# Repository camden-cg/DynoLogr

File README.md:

# DynoLogr

DynoLogr is an ESP32-based vehicle telemetry project with an OLED interface and
a browser dashboard.

## Repository layout

- `firmware/DynoLogr/` contains the Arduino sketch. `DynoLogr.ino` holds shared
  configuration and state; the other `.ino` tabs group control, IMU, display,
  web API, and application code.
- `firmware/prototypes/` contains the standalone OLED/MPU prototype sketch.
- `software/` contains the browser dashboard and its CSS and JavaScript.
- `electronics/` contains the KiCad board file.
- `docs/images/` contains project images.

## Firmware

Open `firmware/DynoLogr/DynoLogr.ino` in Arduino IDE. This sketch uses
Bluepad32, which requires its ESP32 board package; installing a `Bluepad32`
library in the sketchbook `libraries` folder is not sufficient.

In Arduino IDE settings, add both board package URLs:

- `https://raw.githubusercontent.com/espressif/arduino-esp32/gh-pages/package_esp32_index.json`
- `https://raw.githubusercontent.com/ricardoquesada/esp32-arduino-lib-builder/master/bluepad32_files/package_esp32_bluepad32_index.json`

In Boards Manager, install `esp32` and `esp32_bluepad32`. Then select **DOIT
ESP32 DEVKIT V1** from the **ESP32 + Bluepad32 Arduino** board menu, rather
than selecting the same board from the regular Espressif board menu. See the
[Bluepad32 Arduino setup guide](https://bluepad32.readthedocs.io/en/latest/plat_arduino/).

Install the remaining libraries included by the sketch: Adafruit GFX,
Adafruit SSD1306, Adafruit MPU6050, Adafruit Unified Sensor, ESP32Servo, and
ArduinoJson. The ESP32 Arduino core provides Wire, WiFi, and WebServer.

Copy `firmware/DynoLogr/Credentials.example.h` to
`firmware/DynoLogr/Credentials.h` and set `WIFI_SSID` and `WIFI_PASS` there.
`Credentials.h` is ignored by Git and should remain local. The firmware continues
to run without Wi-Fi.

## Dashboard

Open `software/index.html` in a browser. Connect to the ESP32's network address
using the dashboard connection controls.

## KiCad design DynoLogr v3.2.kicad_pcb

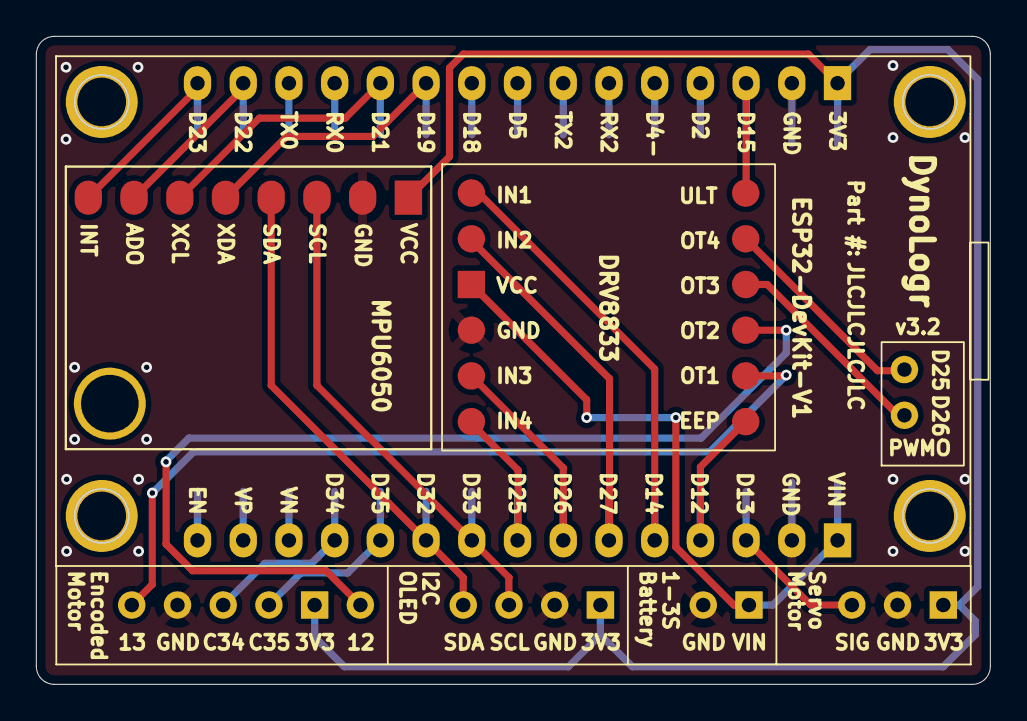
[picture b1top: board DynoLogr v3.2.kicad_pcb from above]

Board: 2 copper layers, 53.0 x 36.0 mm, 4 parts (0 on the bottom side), 25 nets.

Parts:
DRV8833: DRV8833
ESP32, ESP32-DevKit-V1: ESP32 30; ESP32_30pin
MPU6050: MPU6050

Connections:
2: ESP32.2 (D2), ESP32-DevKit-V1.2 (D2)
4: ESP32.4 (D4-), ESP32-DevKit-V1.4 (D4-)
/3V3: ESP32.3V3, ESP32-DevKit-V1.3V3, MPU6050.+ (VCC)
/BO: DRV8833.VCC, ESP32.VIN, ESP32-DevKit-V1.VIN
/EC1: ESP32.34 (D34), ESP32-DevKit-V1.34 (D34)
/EC2: ESP32.35 (D35), ESP32-DevKit-V1.35 (D35)
/EEP: DRV8833.EEP, ESP32.12 (D12), ESP32-DevKit-V1.12 (D12)
/GND: DRV8833.GND, ESP32.GND, ESP32.GND2 (GND), ESP32-DevKit-V1.GND, ESP32-DevKit-V1.GND2 (GND), MPU6050.- (GND)
/IN1: DRV8833.IN1, ESP32.14 (D14), ESP32-DevKit-V1.14 (D14)
/IN2: DRV8833.IN2, ESP32.27 (D27), ESP32-DevKit-V1.27 (D27)
/IN3: DRV8833.IN3, ESP32.26 (D26), ESP32-DevKit-V1.26 (D26)
/IN4: DRV8833.IN4, ESP32.25 (D25), ESP32-DevKit-V1.25 (D25)
/INT: ESP32.23 (D23), ESP32-DevKit-V1.23 (D23), MPU6050.23 (INT)
/SCL: ESP32.33 (D33), ESP32-DevKit-V1.33 (D33), MPU6050.22 (SCL)
/SDA: ESP32.32 (D32), ESP32-DevKit-V1.32 (D32), MPU6050.21 (SDA)
/SPWM: ESP32.13 (D13), ESP32-DevKit-V1.13 (D13)
AD0: ESP32.22 (D22), ESP32-DevKit-V1.22 (D22), MPU6050.3 (ADO)
EN: ESP32.EN, ESP32-DevKit-V1.EN
unnamed: ESP32.5 (D5), ESP32-DevKit-V1.5 (D5)
unnamed: ESP32.18 (D18), ESP32-DevKit-V1.18 (D18)
ULT: DRV8833.6 (ULT), ESP32.15 (D15), ESP32-DevKit-V1.15 (D15)
XCL: ESP32.21 (D21), ESP32-DevKit-V1.21 (D21), MPU6050.2 (XCL)
XDA: ESP32.19 (D19), ESP32-DevKit-V1.19 (D19), MPU6050.1 (XDA)
vn: ESP32.VN, ESP32-DevKit-V1.VN
vp: ESP32.VP, ESP32-DevKit-V1.VP
